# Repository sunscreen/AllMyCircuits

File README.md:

https://kicanvas.org/?github=https%3A%2F%2Fgithub.com%2Fsunscreen%2FAllMyCircuits

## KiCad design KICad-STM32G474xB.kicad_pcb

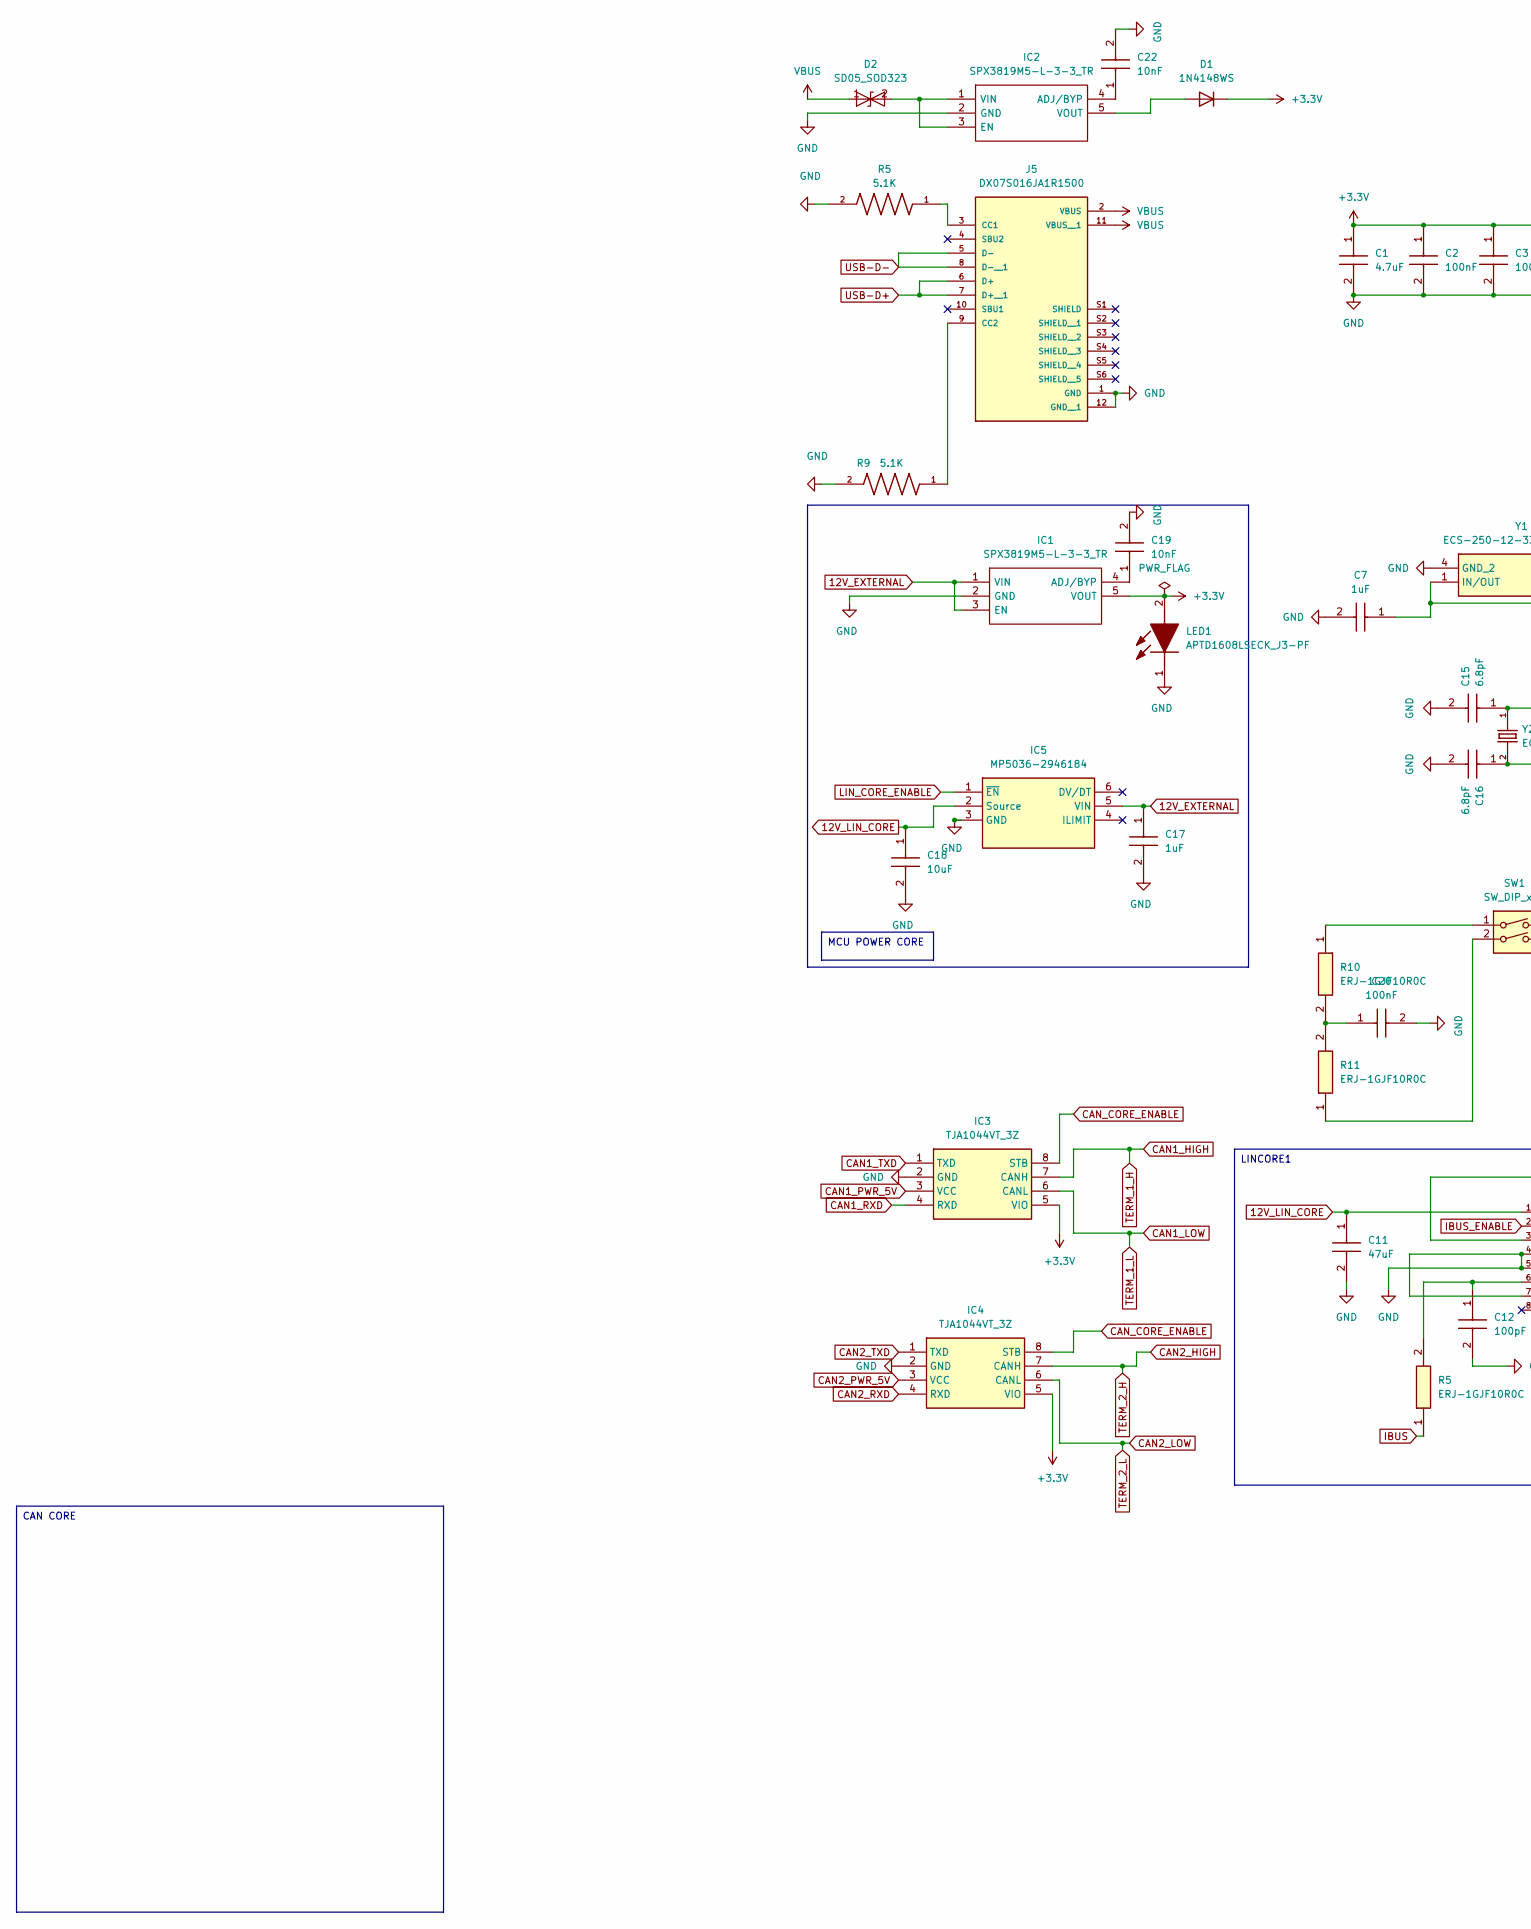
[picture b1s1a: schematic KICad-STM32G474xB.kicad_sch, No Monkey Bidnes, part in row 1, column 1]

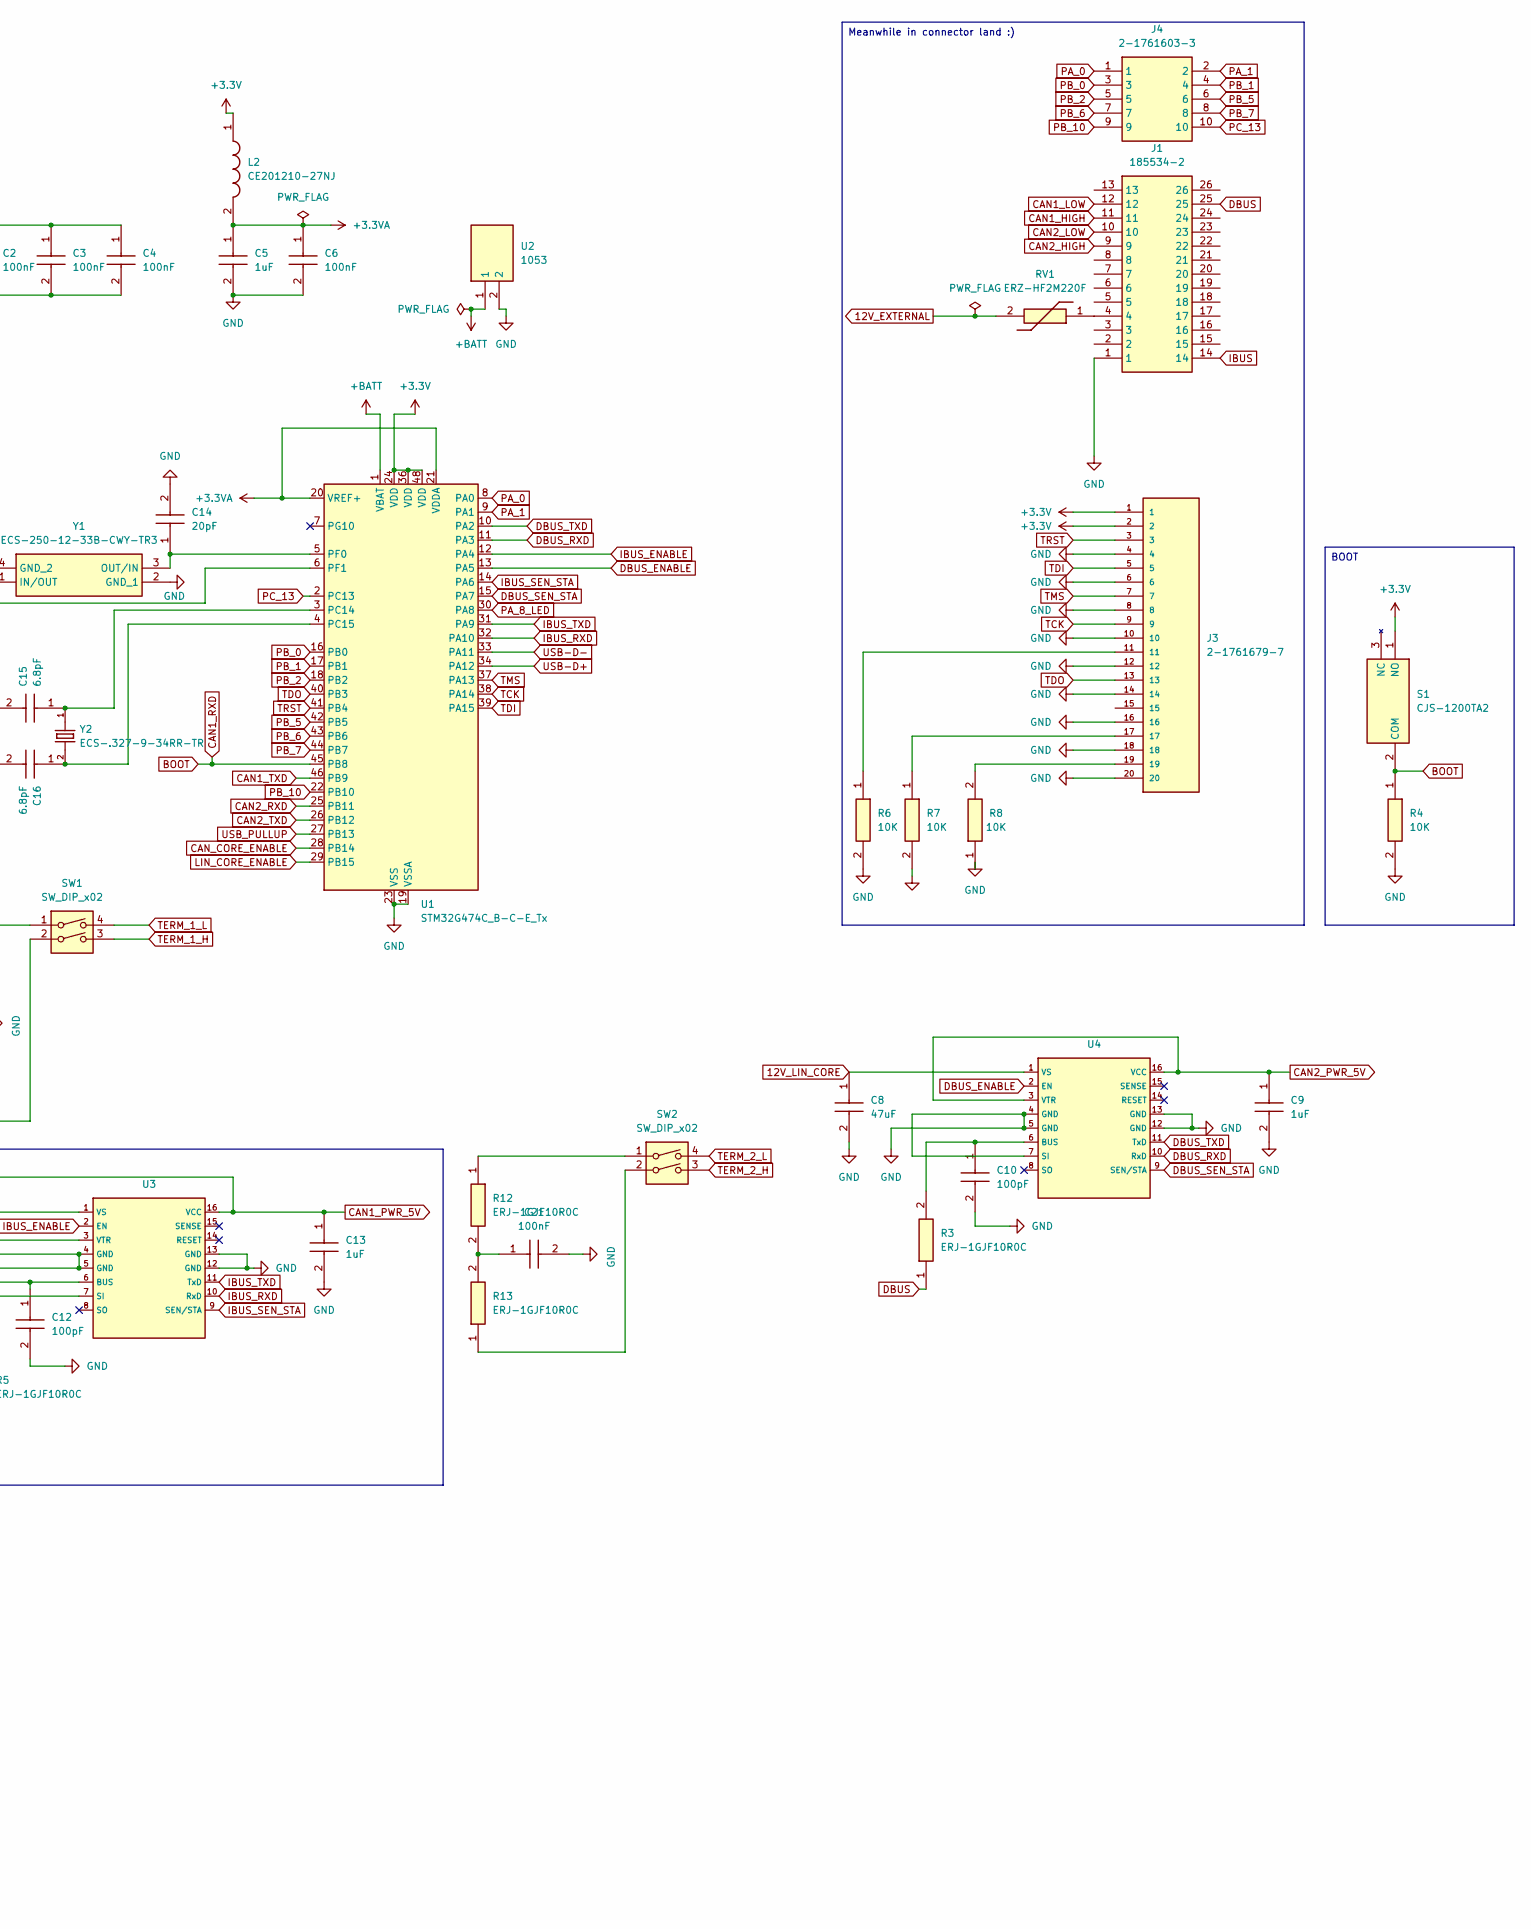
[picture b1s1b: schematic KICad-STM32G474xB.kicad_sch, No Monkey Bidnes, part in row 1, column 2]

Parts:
C1: 4.7uF; CAPC1005X55N; Manufacturer_Part_Number 885012205085R
C2, C3, C4, C6, C20, C21: 100nF; CAPC1005X55N; Manufacturer_Part_Number 885012205085R
C5, C7, C9, C13, C17: 1uF; CAPC1005X55N; Manufacturer_Part_Number 885012205085R
C8, C11: 47uF; CAPC1005X55N; Manufacturer_Part_Number 885012205085R
C10, C12: 100pF; CAPC1005X55N; Manufacturer_Part_Number 885012205085R
C14: 20pF; CAPC1005X55N; Manufacturer_Part_Number 885012205085R
C15, C16: 6.8pF; CAPC1005X55N; Manufacturer_Part_Number 885012205085R
C18: 10uF; CAPC1005X55N; Manufacturer_Part_Number 885012205085R
C19, C22: 10nF; CAPC1005X55N; Manufacturer_Part_Number 885012205085R
D1: 1N4148WS; D_SOD-323
D2: SD05_SOD323; D_SOD-323
IC1, IC2: SPX3819M5-L-3-3_TR; SOT95P280X145-5N; Mouser Part Number 701-SPX3819M5-L-33TR
IC3, IC4: TJA1044VT_3Z; SO-8_3.9x4.9mm_P1.27mm; Mouser Part Number 771-TJA1044VT/3Z
IC5: MP5036-2946184; SOT-23-6_Handsoldering; Mouser Part Number 946-MP5094GJ-Z
J1: 185534-2; 1855342; Mouser Part Number 571-185534-2
J3: 2-1761679-7; TE_2-1761679-7; PARTREV R
J4: 2-1761603-3; SHDR10W79P254_2X5_2032X916X922P; Mouser Part Number 571-2-1761603-3
J5: DX07S016JA1R1500; JAE_DX07S016JA1R1500; PARTREV 1
L2: CE201210-27NJ; INDC2012X103N; Mouser Part Number 652-CE201210-27NJ
LED1: APTD1608LSECK_J3-PF; APT1608CGCK; Mouser Part Number 604-APTD1608LSECKJ3F
R3, R10, R11, R12, R13: ERJ-1GJF10R0C; ERJ1GJJ2R4C; Mouser Part Number 667-ERJ-1GJF10R0C
R4, R6, R7, R8: 10K; ERJ1GJJ2R4C; Mouser Part Number 667-ERJ-1GJF10R0C
R5, R9: 5.1K; RES_ERA3AEB121V; PARTREV 3/1/2020
RV1: ERZ-HF2M220F; ERZHF2M220F; Mouser Part Number 667-ERZ-HF2M220F
S1: CJS-1200TA2; CJS1200TA2; Mouser Part Number 229-CJS-1200TA2
SW1, SW2: SW_DIP_x02; SW_DIP_SPSTx02_Slide_Copal_CHS-02A_W5.08mm_P1.27mm_JPin
U1: STM32G474C_B-C-E_Tx; LQFP-48_7x7mm_P0.5mm
U2: 1053; Mouser Part Number 534-1053-BH
U3, U4: SOIC-16W_7.5x10.3mm_P1.27mm
Y1: ECS-250-12-33B-CWY-TR3; ECS2501233BCWYTR3; Mouser Part Number 520-EC2501233BCWYTR3
Y2: ECS-.327-9-34RR-TR; XTAL_ECS-.327-9-34RR-TR

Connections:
12V_EXTERNAL: C17.1, IC1.1 (VIN), IC1.3 (EN), IC5.5 (VIN), RV1.2
12V_LIN_CORE: C8.1, C11.1, C18.1, IC5.2 (Source), U3.1 (VS), U4.1 (VS)
+3.3V: C1.1, C2.1, C3.1, C4.1, D1.1 (K), IC1.5 (VOUT), IC3.5 (VIO), IC4.5 (VIO), J3.1, J3.2, L2.1, LED1.2 (A), S1.1 (NO), U1.24 (VDD), U1.36 (VDD), U1.48 (VDD)
+3.3VA: C5.1, C6.1, L2.2, U1.20 (VREF+), U1.21 (VDDA)
+BATT: U1.1 (VBAT), U2.1
BOOT: IC3.4 (RXD), R4.1, S1.2 (COM), U1.45 (PB8)
CAN1_HIGH: IC3.7 (CANH), J1.11, SW1.3
CAN1_LOW: IC3.6 (CANL), J1.12, SW1.4
CAN1_PWR_5V: C13.1, IC3.3 (VCC), U3.3 (VTR), U3.16 (VCC)
CAN1_TXD: IC3.1 (TXD), U1.46 (PB9)
CAN2_HIGH: IC4.7 (CANH), J1.9, SW2.3
CAN2_LOW: IC4.6 (CANL), J1.10, SW2.4
CAN2_PWR_5V: C9.1, IC4.3 (VCC), U4.3 (VTR), U4.16 (VCC)
CAN2_RXD: IC4.4 (RXD), U1.25 (PB11)
CAN2_TXD: IC4.1 (TXD), U1.26 (PB12)
CAN_CORE_ENABLE: IC3.8 (STB), IC4.8 (STB), U1.28 (PB14)
DBUS: J1.25, R3.1
DBUS_ENABLE: U1.13 (PA5), U4.2 (EN)
DBUS_RXD: U1.11 (PA3), U4.10 (RxD)
DBUS_SEN_STA: U1.15 (PA7), U4.9 (SEN/STA)
DBUS_TXD: U1.10 (PA2), U4.11 (TxD)
IBUS_ENABLE: U1.12 (PA4), U3.2 (EN)
IBUS_RXD: U1.32 (PA10), U3.10 (RxD)
IBUS_SEN_STA: U1.14 (PA6), U3.9 (SEN/STA)
IBUS_TXD: U1.31 (PA9), U3.11 (TxD)
LIN_CORE_ENABLE: IC5.1 (~EN), U1.29 (PB15)
unnamed: C20.1, R10.2, R11.2
unnamed: C21.1, R12.2, R13.2
unnamed: D1.2 (A), IC2.5 (VOUT)
unnamed: D2.2 (A2), IC2.1 (VIN), IC2.3 (EN)
unnamed: C19.1, IC1.4 (ADJ/BYP)
unnamed: C22.1, IC2.4 (ADJ/BYP)
unnamed: J1.4, RV1.1
unnamed: J3.11, R6.1
unnamed: J3.17, R7.1
unnamed: J3.19, R8.2
unnamed: R10.1, SW1.1
unnamed: R11.1, SW1.2
unnamed: R12.1, SW2.1
unnamed: R13.1, SW2.2
unnamed: C15.1, U1.3 (PC14), Y2.1
unnamed: C16.1, U1.4 (PC15), Y2.2
unnamed: C14.1, U1.5 (PF0), Y1.3 (OUT/IN)
unnamed: C7.1, U1.6 (PF1), Y1.1 (IN/OUT)
unnamed: C10.1, R3.2, U4.6 (BUS)
PA_0: J4.1, U1.8 (PA0)
PA_1: J4.2, U1.9 (PA1)
PA_8_LED: U1.30 (PA8)
PB_0: J4.3, U1.16 (PB0)
PB_1: J4.4, U1.17 (PB1)
PB_2: J4.5, U1.18 (PB2)
PB_5: J4.6, U1.42 (PB5)
PB_6: J4.7, U1.43 (PB6)
PB_7: J4.8, U1.44 (PB7)
PB_10: J4.9, U1.22 (PB10)
PC_13: J4.10, U1.2 (PC13)
TCK: J3.9, U1.38 (PA14)
TDI: J3.5, U1.39 (PA15)
TDO: J3.13, U1.40 (PB3)
TMS: J3.7, U1.37 (PA13)
TRST: J3.3, U1.41 (PB4)
USB-D+: U1.34 (PA12); also elsewhere on the board
USB-D-: U1.33 (PA11); also elsewhere on the board
USB_PULLUP: U1.27 (PB13)
VBUS: D2.1 (A1); also elsewhere on the board

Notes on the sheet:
MCU POWER CORE
LINCORE1
CAN CORE
Meanwhile in connector land :)
BOOT

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
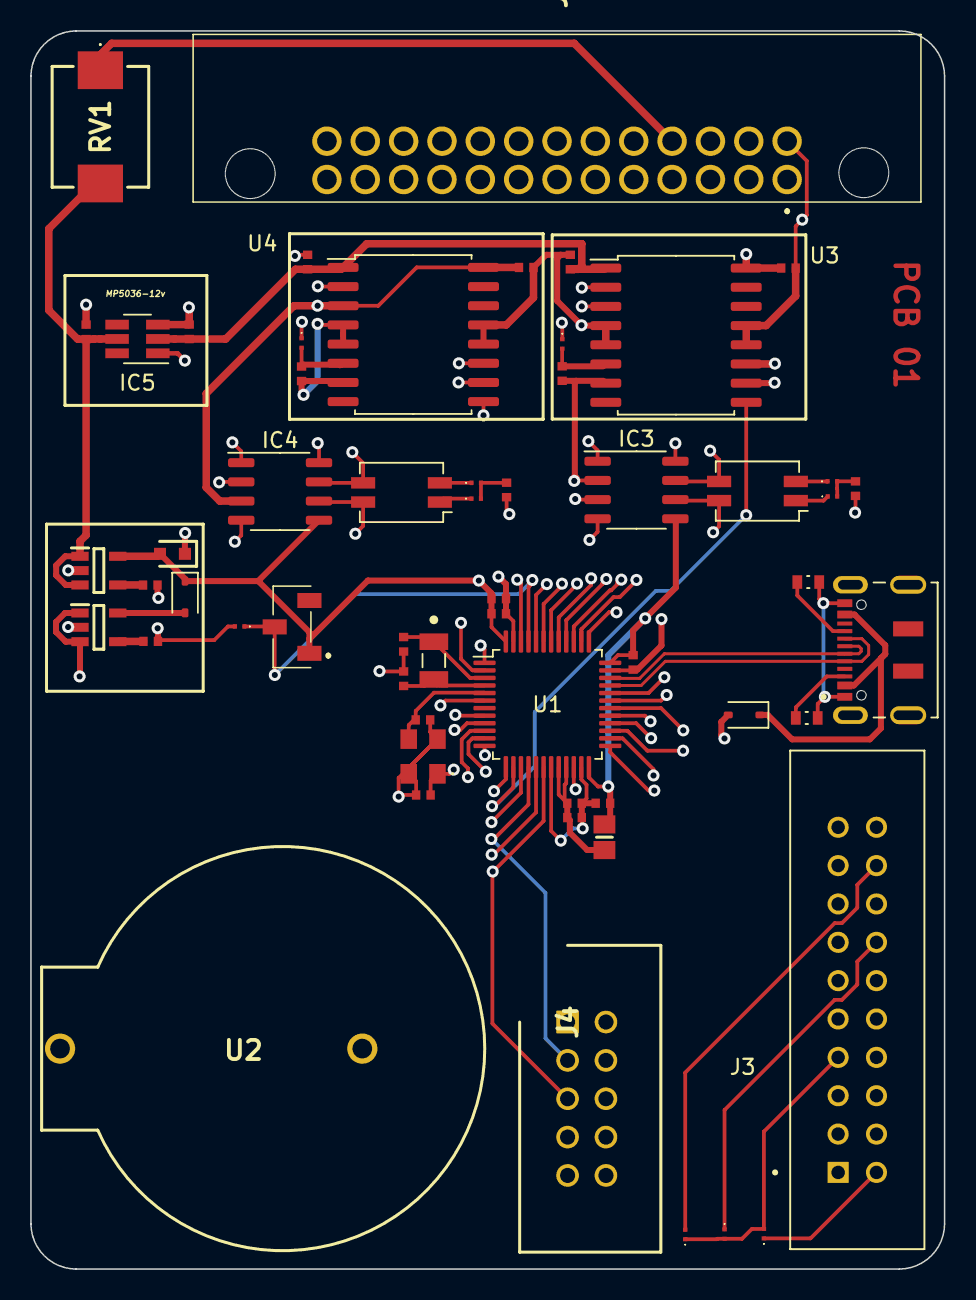
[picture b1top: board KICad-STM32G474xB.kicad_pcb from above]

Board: 4 copper layers, 60.5 x 82.0 mm, 57 parts (0 on the bottom side), 68 nets.

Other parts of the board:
J2: DX07S016JA1R1500; JAE_DX07S016JA1R1500
R1, R2: 5.1K; RES_ERA3AEB121V

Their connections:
unnamed: J2.9 (CC2), R2.1
USB-D+: J2.6 (D+), J2.7 (D+__1); also elsewhere on the board
USB-D-: J2.5 (D-), J2.8 (D-__1); also elsewhere on the board
VBUS: J2.2 (VBUS), J2.11 (VBUS__1); also elsewhere on the board

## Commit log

2023-12-27 Create blabla
2023-12-27 Rename blabla to blabla.c
